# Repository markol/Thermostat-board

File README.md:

## Thermostat board on AVR atmega MCU
Digital temperature controler. Powered from mains network, can be build into DIY hardware or appiliances like fridge or oven. Easy to at home make, non precsion requiring THT desin with numeric 7-segment LED display, 2 control buttons, buzzer and rotary encoder for temp adjustment. Temperature is measured by one or two thermistors, all processing is done by atmega8 microcontroller or similar. Look also [here](http://github.com/markol/Thermostat-firmware) for firmware for this board. 

Design is made with KiCad, remember to add project footprint libraries (from *custom_fp.pretty* directory) when opening first time.

Currently project has only one master branch, other may appear when development proceed.

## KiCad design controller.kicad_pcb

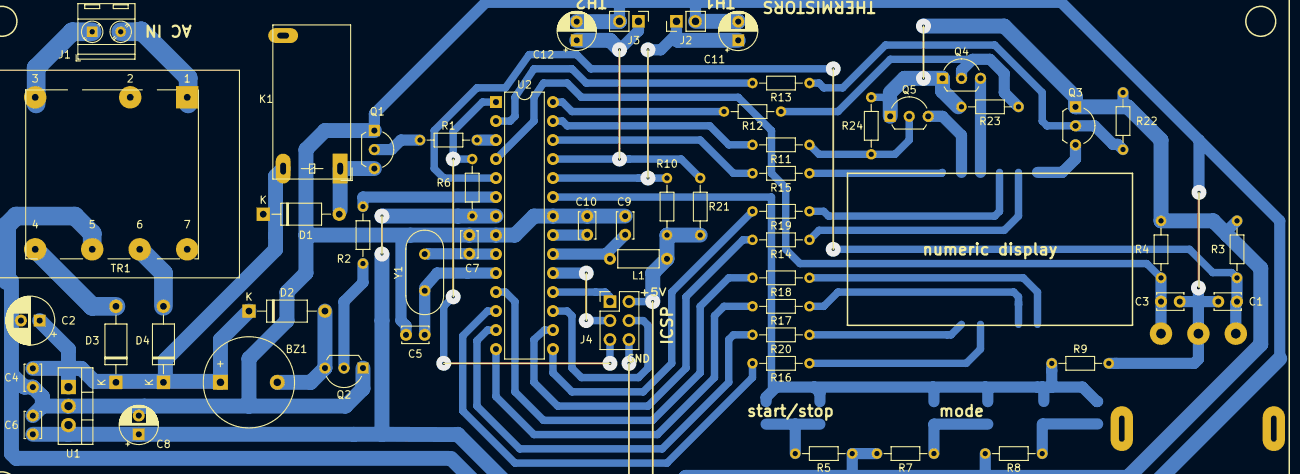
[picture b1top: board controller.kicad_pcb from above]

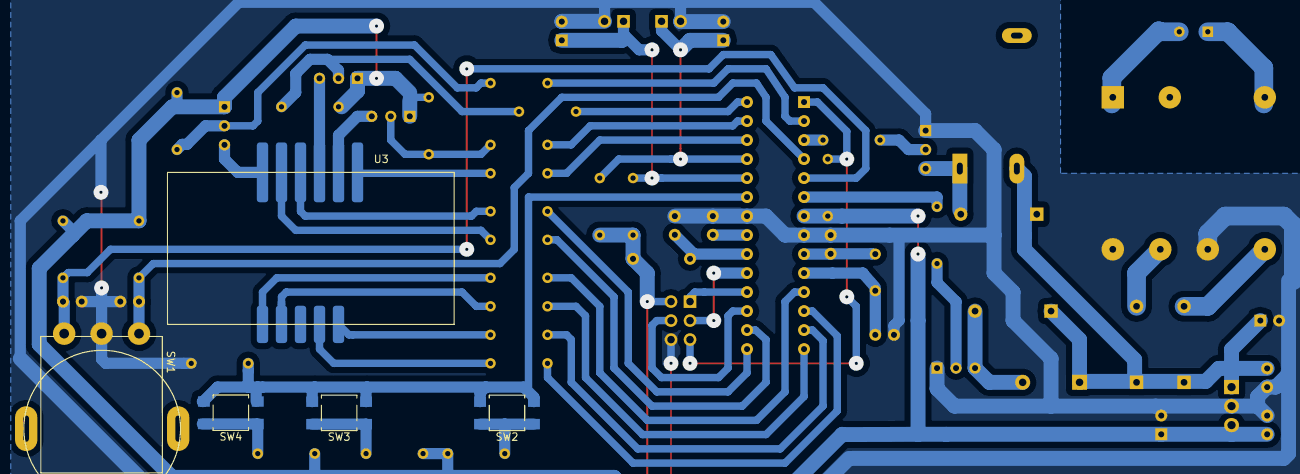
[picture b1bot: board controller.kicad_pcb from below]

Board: 2 copper layers, 61 parts (5 on the bottom side), 52 nets.

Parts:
BZ1: Buzzer; Buzzer_12x9.5RM7.6
C1, C3, C4, C6, C9, C10: 100nF; C_Disc_D3.4mm_W2.1mm_P2.50mm
C2: 100uF; CP_Radial_D6.3mm_P2.50mm
C5, C7: 22pF; C_Disc_D3.4mm_W2.1mm_P2.50mm
C8, C11, C12: 10uF; CP_Radial_D5.0mm_P2.50mm
D1, D2, D3, D4: D; D_A-405_P10.16mm_Horizontal
J1: AC_PWR; TerminalBlock_MetzConnect_Type086_RT03402HBLC_1x02_P3.81mm_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
J2: THERMISTOR1; PinHeader_1x02_P2.54mm_Vertical
J3: THERMISTOR2; PinHeader_1x02_P2.54mm_Vertical
J4: AVR_ICSP; PinHeader_2x03_P2.54mm_Vertical
K1: FRT5_separated; Relay_Omron
L1: L; L_Axial_L5.3mm_D2.2mm_P7.62mm_Horizontal_Vishay_IM-1
Q1, Q2: S9013; TO-92L_Inline_Wide
Q3, Q4, Q5: S9015; TO-92L_Inline_Wide
R1, R2: 4k7; R_Axial_DIN0204_L3.6mm_D1.6mm_P7.62mm_Horizontal
R3, R4, R5, R6: 10k; R_Axial_DIN0204_L3.6mm_D1.6mm_P7.62mm_Horizontal
R7: 22k; R_Axial_DIN0204_L3.6mm_D1.6mm_P7.62mm_Horizontal
R8: 47k; R_Axial_DIN0204_L3.6mm_D1.6mm_P7.62mm_Horizontal
R9: 100k; R_Axial_DIN0204_L3.6mm_D1.6mm_P7.62mm_Horizontal
R10, R21: 4.7k; R_Axial_DIN0204_L3.6mm_D1.6mm_P7.62mm_Horizontal
R11, R12, R13, R22, R23, R24: 3k3; R_Axial_DIN0204_L3.6mm_D1.6mm_P7.62mm_Horizontal
R14, R15, R16, R17, R18, R19, R20: 330; R_Axial_DIN0204_L3.6mm_D1.6mm_P7.62mm_Horizontal
SW1: Rotary_Encoder; Encoder_Vertical
SW2: START/STOP; SW_SPST_TL3305A
SW3: MODE; SW_SPST_TL3305A
SW4: SW_Push; SW_SPST_TL3305A
TR1: dmr-63; Transformer_7pin
U1: L7805; TO-220-3_Vertical
U2: ATmega8L-8PU; DIP-28_W7.62mm
U3: 3digit11pin
Y1: Crystal; Crystal_HC18-U_Vertical

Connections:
+5V: C6.1, C8.1, J4.2, L1.1, Q3.1, Q4.1, Q5.1, R3.2, R4.2, R5.2, R6.1, R7.2, R8.2, R10.1, R21.1, R22.2, R23.2, R24.2, U1.3, U2.7
/BUZZER: R2.2, U2.6
/DIGIT1: R13.2, U2.2
/DIGIT2: R12.2, U2.28
/DIGIT3: R11.2, U2.27
/DIGIT_A: R14.2, U2.16
/DIGIT_B: R15.2, U2.26
/DIGIT_C: R16.2, U2.12
/DIGIT_D: R17.2, U2.14
/DIGIT_E: R18.2, U2.11
/DIGIT_F: R19.2, U2.15
/DIGIT_G: R20.2, U2.13
/ENCODER_A: C3.1, R4.1, SW1.A, U2.4
/ENCODER_B: C1.1, R3.1, SW1.B, U2.5
/KEYS: R9.2, SW2.2, SW3.2, SW4.2, U2.23
/MISO: J4.1, U2.18
/MOSI: J4.4, U2.17
/RELAY: R1.2, U2.3
/RESET: J4.5, R6.2, U2.1
/SCK: J4.3, U2.19
/SENSOR1: C11.1, J2.1, R10.2, U2.24
/SENSOR2: C12.1, J3.1, R21.2, U2.25
GND: C1.2, C2.2, C3.2, C4.2, C5.2, C6.2, C7.2, C8.2, C9.2, C10.2, C11.2, C12.2, J2.2, J3.2, J4.6, Q1.1, Q2.1, R9.1, SW1.C, TR1.5, TR1.7, U1.2, U2.8, U2.22
unnamed: BZ1.2, D2.2, Q2.3
unnamed: C5.1, U2.10, Y1.1
unnamed: C7.1, U2.9, Y1.2
unnamed: C9.1, L1.2, U2.20
unnamed: C10.1, U2.21
unnamed: D1.2, K1.10, Q1.3
unnamed: D3.2, TR1.4
unnamed: D4.2, TR1.6
unnamed: J1.1, TR1.3
unnamed: J1.2, TR1.1
unnamed: Q1.2, R1.1
unnamed: Q2.2, R2.1
unnamed: Q3.2, R13.1, R22.1
unnamed: Q3.3, U3.1
unnamed: Q4.2, R12.1, R23.1
unnamed: Q4.3, U3.4
unnamed: Q5.2, R11.1, R24.1
unnamed: Q5.3, U3.5
unnamed: R5.1, SW2.1
unnamed: R7.1, SW3.1
unnamed: R8.1, SW4.1
unnamed: R14.1, U3.2
unnamed: R15.1, U3.6
unnamed: R16.1, U3.10
unnamed: R17.1, U3.8
unnamed: R18.1, U3.7
unnamed: R19.1, U3.3
unnamed: R20.1, U3.11
VDD: BZ1.1, C2.1, C4.1, D1.1, D2.1, D3.1, D4.1, K1.1, U1.1
